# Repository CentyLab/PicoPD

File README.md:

# PicoPD
Pico PD is a development board for USB Power Delivery development with Raspberry Pi Pico footprint. The board can help you negotiate voltage from USB PD 2.0, 3.0, and 3.1 with PPS (programable power supply) up to 5A of current at 20V max. The board feature input current/voltage/temperture reading as well as power switch to cut of the current to external devices.

# Quick links
[AP33772 Library](https://github.com/CentyLab/AP33772-Cpp)

[PicoPD Pinout](#picopd-pinout)

[Setup for AP33772 objects](#setup-for-ap33772-objects)

[Basic AP33772 functions](#basic-ap33772-functions)

[Important note](#important-note)

[Arduino IDE setup](#arduino-ide-setup)

[VSCode PlatformIO setup](#vscode-platformio-setup)

[Enable Serial print for debugging](#enable-serial-debug)

# Pin out

# Setup for AP33772 objects
To use AP33772 IC with the library, first you need to create a `usbpd` object. Then set up your I2C pins and start collecting the power profiles from your charger. Ensure your delay after `Wire.begin()` is more than 500ms for stable PDOs request. Enable pin 23 to allow VBUS pass-through.
```
AP33772 usbpd; // Automatically wire to Wire0

void setup()
{
  Wire.setSDA(0); // Set the correct SDA0 pin
  Wire.setSCL(1); // Set the correct SCL0 pin
  Wire.begin();
  Serial.begin(115200);
  delay(1000); 		// Delay is needed for the IC to obtain PDOs
  usbpd.begin(); 	// Start pulling the PDOs from power supply

  pinMode(25, OUTPUT); // Built in LED
  pinMode(23, OUTPUT); // Load Switch
  digitalWrite(23, HIGH); // Turn on VBUS pin

  usbpd.printPDO(); //Print out PDO to Serial port
}
```

# Basic AP33772 functions
Common functions are:
```
setVoltage(int targetVoltage)       //Set voltage, unit in mV, read libary for logic flow
setMaxCurrent(int targetMaxCurrent) //Allow current limit if source has that capability
readVoltage()                       //Return voltage in mV
readCurrent()                       //Return current in mA
printPDO()                          //Print out PDOs in Serial
```

Set over tempearture protection
```
usbpd.setOTPTHR(100);               //Turn off output if NTC detect 100C or above
usbpd.setMask(OTP_EN);              //Enable Over Temp Protection flag
```

# Important note
After flashing, the latest AP33772-CPP has been updated to auto request PDO after bootup without reconnecting the charger. Thank to @Patronics contribution.

Calling `usbpd.printPDO()` without `Serial.begin()` can soft-brick your PicoPD. Causing the IC to be non-recognizable by your computer. You will have to use PicoProbe to reflash the chip. Check out @Patronics [PicoProbePCB](https://github.com/Patronics/PicoProbePCB) if you would like to make a stable fixture for firmware debugging.

# Enable Serial Debug

To enable Serial debug, there are 3 main methods:

**Using USB-C Power/Data splitter (easiest):** Use a USB-C Splitter that separates the USB 2.0 signal into another USB-C port. You only need USB 2.0 FullSpeed (12Mbps) for the job, but never hurts to get extra speed if needed later. 

* [USB-C Power/Data Splitter](https://lectronz.com/products/usb-c-splitter) (USB-HighSpeed)
* [USB-C PD Power Splitter](https://www.tindie.com/products/essenceeng/usb-c-pd-power-splitter/) (USB-HighSpeed)

**Using the provided solder pads at the back:** Desolder the front "USB Jumper" resistors. They are just 2x 0 Ohm resistors that bridge between the RP2040 IC and the USB-C port. Then use a [USB Type A Plug Breakout Cable](https://www.adafruit.com/product/4448?gclid=Cj0KCQjwoK2mBhDzARIsADGbjeo7nigl8f-8mf8ojsnPvi8TiROBC7YXmMKpGVau8VJHeIO8NyU5nncaAs9qEALw_wcB), or make your own from any USB cable and connect to the existing pad at the back of PicoPD

**Using UART communication**: Make sure you are not using GP0 and GP1 as they are reserved for I2C0 channel for AP33772 IC. Check out Youtube tutorial: [Talk to Your Pico Over Serial](https://www.youtube.com/watch?v=pbWhoJdYA1s)

# Arduino IDE setup
Open Arduino IDE, select File -> Preference

Copy this line below and place in "Aditional Boards Manager URLs" -> OK. This will allow you to pull the Earlephilhower Pico core that work with the AP33772 library.

```
https://github.com/earlephilhower/arduino-pico/releases/download/global/package_rp2040_index.json
```

From Board Manager, search for "Pico" and install the "Raspberry Pi Pico/RP2040" core by Earlephilhower

Now from Tool -> Board -> Raspberry Pi Pico/RP2040 -> Raspberry Pi Pico

Now download the latest AP33772 library as a Zip file

```
https://github.com/CentyLab/AP33772-Cpp
```

Import the AP33772 library into your Arduino IDE. Sketch -> Include library -> Add .ZIP Library ...

Now you start using the Example code in File -> Examples -> AP33772-Cpp-main. The example is ready to compile and flash on to your PicoPD.

Now you can plug in your USB-C cable with Power Delivery 2.0/3.0/3.1. If you also like to have serial print out, check out [Enable Serial print for debugging](#enable-serial-debug).

# VSCode PlatformIO setup
After [VSCode](https://code.visualstudio.com/) installation, you will need to install PlatformIO extension.

Now create a new PlatformIO project
+ Name:WhatEverYouWantToCallit
+ Board: Pico (RasberryPi)
+ Framework: Arduino (default)

Click "Finish"

In your new project, copy this and replace everything in platformio.ini. This is how you ask PlatformIO to compile using Earlephilhower Pico core, and enable upload via USB.

```
[env:pico]
platform = https://github.com/maxgerhardt/platform-raspberrypi.git
board = pico
framework = arduino
board_build.core = earlephilhower

;; If directly upload from PC
upload_protocol = picotool
```

Now download the latest AP33772 library as a Zip file. Unzip and place the folder in `lib`

```
https://github.com/CentyLab/AP33772-Cpp
```

Your lib folder should look like this

To try out example code, you copy the content inside `lib/Compiled for PicoPD/PPSCycling/PPSCycling.ino`, And replace everything in your `src/main.cpp`

Now you can plug the PicoPD to your computer via USB-C and hit the upload button. After this, you will have to connect a charger to PicoPD to see the voltage cycling example. If you also like to have serial print out, check out [Enable Serial print for debugging](#enable-serial-debug).

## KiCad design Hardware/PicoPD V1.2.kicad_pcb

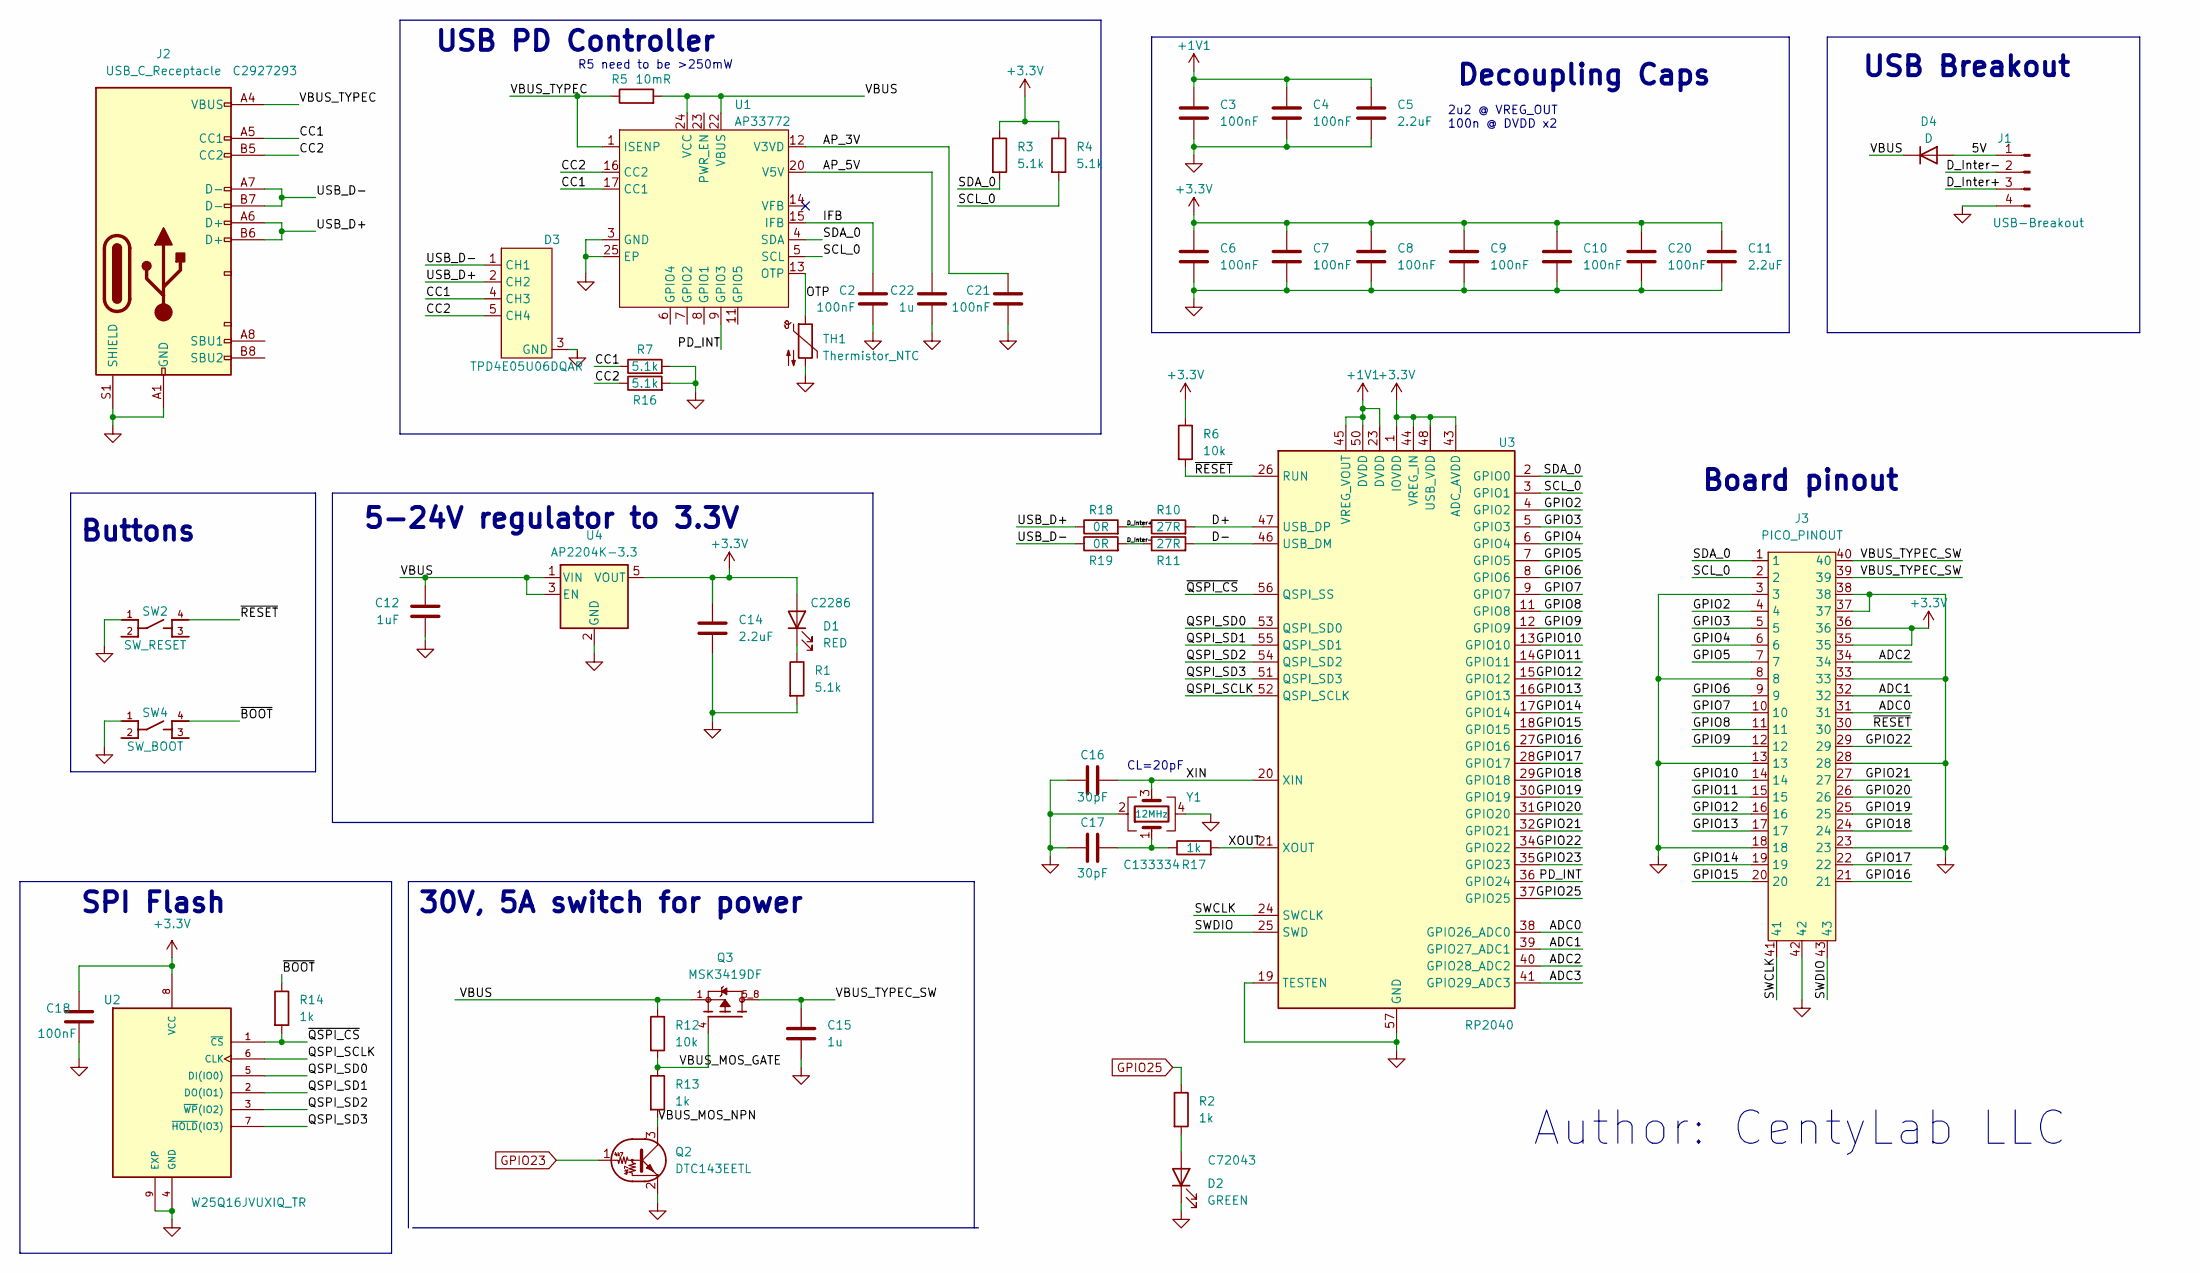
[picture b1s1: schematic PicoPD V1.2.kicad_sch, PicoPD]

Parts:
C2, C3, C4, C6, C7, C8, C9, C10, C18, C20, C21: 100nF; C_0402_1005Metric; LCSC C1525
C5, C11: 2.2uF; C_0402_1005Metric; LCSC C12530
C12: 1uF; C_0603_1608Metric; Voltage 50V; LCSC C15849
C14: 2.2uF; C_0603_1608Metric; Voltage 16V; LCSC C23630
C15, C22: 1u; C_0603_1608Metric; LCSC C15849
C16, C17: 30pF; C_0402_1005Metric; LCSC C1570
D1: RED; LED_0603_1608Metric; LCSC C2286
D2: GREEN; LED_0603_1608Metric; LCSC C72043
D3: TPD4E05U06DQAR; SON50P100X255X50-10N; LCSCAlternative1 C478014
D4: D; D_SOD-123; LCSC C8598
J1: USB-Breakout; 1x4_2.54mmHorizontalSMD
J2: USB_C_Receptacle; YTC-TC16S-28; LCSC C2927293
J3: PICO_PINOUT; PICO_Thru
Q2: DTC143EETL; SOT-416; LCSC C2991940
Q3: MSK3419DF; TRANS_AON7403; PARTREV G; LCSC C2902915
R1, R3, R4, R7, R16: 5.1k; R_0402_1005Metric; LCSC C25905
R2, R13, R14, R17: 1k; R_0402_1005Metric; LCSC C11702
R5: 10mR; R_0805_2012Metric; LCSC C728271
R6, R12: 10k; R_0402_1005Metric; LCSC C25744
R10, R11: 27R; R_0402_1005Metric; LCSC C138021
R18, R19: 0R; R_0402_1005Metric; LCSC C17168
SW2: SW_RESET; SW_PTS810_SJM_250_SMTR_LFS; LCSC C221896
SW4: SW_BOOT; SW_PTS810_SJM_250_SMTR_LFS; LCSC C221896
TH1: Thermistor_NTC; R_0402_1005Metric; LCSC C77131
U1: AP33772; QFN-24-1EP_4x4mm_P0.5mm_EP2.6x2.6mm
U2: W25Q16JVUXIQ_TR; IC_W25Q16JVUXIQ_TR; PARTREV H; LCSC C2843335
U3: RP2040; QFN-56-1EP_7x7mm_P0.4mm_EP3.2x3.2mm; LCSC C2040
U4: AP2204K-3.3; SOT-23-5; JLCPCB Rotation Offset 180
Y1: 12MHz; Crystal_SMD_3225-4Pin_3.2x2.5mm; LCSC C133334

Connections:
+1V1: C3.1, C4.1, C5.1, U3.23 (DVDD), U3.45 (VREG_VOUT), U3.50 (DVDD)
+3.3V: C6.1, C7.1, C8.1, C9.1, C10.1, C11.1, C14.1, C18.1, C20.1, D1.2 (A), J3.35, J3.36, R3.1, R4.1, R6.1, U2.8 (VCC), U3.1 (IOVDD), U3.10 (IOVDD), U3.22 (IOVDD), U3.33 (IOVDD), U3.42 (IOVDD), U3.43 (ADC_AVDD), U3.44 (VREG_IN), U3.48 (USB_VDD), U3.49 (IOVDD), U4.5 (VOUT)
/5V: D4.2 (A), J1.1
/ADC0: J3.31, U3.38 (GPIO26_ADC0)
/ADC1: J3.32, U3.39 (GPIO27_ADC1)
/ADC2: J3.34, U3.40 (GPIO28_ADC2)
/ADC3: U3.41 (GPIO29_ADC3)
/AP_3V: C21.1, U1.12 (V3VD)
/AP_5V: C22.1, U1.20 (V5V)
/CC1: D3.4 (CH3), D3.7, J2.A5 (CC1), R7.1, U1.17 (CC1)
/CC2: D3.5 (CH4), D3.6, J2.B5 (CC2), R16.1, U1.16 (CC2)
/D+: R10.2, U3.47 (USB_DP)
/D-: R11.2, U3.46 (USB_DM)
/D_Inter+: J1.3, R10.1, R18.2
/D_Inter-: J1.2, R11.1, R19.2
/GPIO2: J3.4, U3.4 (GPIO2)
/GPIO3: J3.5, U3.5 (GPIO3)
/GPIO4: J3.6, U3.6 (GPIO4)
/GPIO5: J3.7, U3.7 (GPIO5)
/GPIO6: J3.9, U3.8 (GPIO6)
/GPIO7: J3.10, U3.9 (GPIO7)
/GPIO8: J3.11, U3.11 (GPIO8)
/GPIO9: J3.12, U3.12 (GPIO9)
/GPIO10: J3.14, U3.13 (GPIO10)
/GPIO11: J3.15, U3.14 (GPIO11)
/GPIO12: J3.16, U3.15 (GPIO12)
/GPIO13: J3.17, U3.16 (GPIO13)
/GPIO14: J3.19, U3.17 (GPIO14)
/GPIO15: J3.20, U3.18 (GPIO15)
/GPIO16: J3.21, U3.27 (GPIO16)
/GPIO17: J3.22, U3.28 (GPIO17)
/GPIO18: J3.24, U3.29 (GPIO18)
/GPIO19: J3.25, U3.30 (GPIO19)
/GPIO20: J3.26, U3.31 (GPIO20)
/GPIO21: J3.27, U3.32 (GPIO21)
/GPIO22: J3.29, U3.34 (GPIO22)
/IFB: C2.1, U1.15 (IFB)
/OTP: TH1.1, U1.13 (OTP)
/PD_INT: U1.9 (GPIO3), U3.36 (GPIO24)
/QSPI_SCLK: U2.6 (CLK), U3.52 (QSPI_SCLK)
/QSPI_SD0: U2.5 (DI(IO0)), U3.53 (QSPI_SD0)
/QSPI_SD1: U2.2 (DO(IO1)), U3.55 (QSPI_SD1)
/QSPI_SD2: U2.3 (~WP(IO2)), U3.54 (QSPI_SD2)
/QSPI_SD3: U2.7 (~HOLD(IO3)), U3.51 (QSPI_SD3)
/SCL_0: J3.2, R4.2, U1.5 (SCL), U3.3 (GPIO1)
/SDA_0: J3.1, R3.2, U1.4 (SDA), U3.2 (GPIO0)
/SWCLK: J3.41, U3.24 (SWCLK)
/SWDIO: J3.43, U3.25 (SWD)
/USB_D+: D3.2 (CH2), D3.9, J2.A6 (D+), J2.B6 (D+), R18.1
/USB_D-: D3.1 (CH1), D3.10, J2.A7 (D-), J2.B7 (D-), R19.1
/VBUS: C12.2, D4.1 (K), Q3.1, Q3.2, Q3.3, R5.2, R12.1, U1.22 (VBUS), U1.24 (VCC), U4.1 (VIN), U4.3 (EN)
/VBUS_MOS_GATE: Q3.4, R12.2, R13.1
/VBUS_MOS_NPN: Q2.3 (C), R13.2
/VBUS_TYPEC: J2.A4 (VBUS), J2.A9 (VBUS), J2.B4 (VBUS), J2.B9 (VBUS), R5.1, U1.1 (ISENP)
/VBUS_TYPEC_SW: C15.1, J3.39, J3.40, Q3.5_8
/XIN: C16.1, U3.20 (XIN), Y1.3
/XOUT: R17.2, U3.21 (XOUT)
/~BOOT: R14.1, SW4.4
/~QSPI_CS: R14.2, U2.1 (~CS), U3.56 (QSPI_SS)
/~RESET: J3.30, R6.2, SW2.4, U3.26 (RUN)
GND: C2.2, C3.2, C4.2, C5.2, C6.2, C7.2, C8.2, C9.2, C10.2, C11.2, C12.1, C14.2, C15.2, C16.2, C17.2, C18.2, C20.2, C21.2, C22.2, D2.1 (K), D3.3 (GND), D3.8 (GND), J1.4, J2.A1 (GND), J2.A12 (GND), J2.B1 (GND), J2.B12 (GND), J2.S1 (SHIELD), J3.3, J3.8, J3.13, J3.18, J3.23, J3.28, J3.33, J3.37, J3.38, J3.42, Q2.2 (E), R1.2, R7.2, R16.2, SW2.1, SW4.1, TH1.2, U1.3 (GND), U1.25 (EP), U2.4 (GND), U2.9 (EXP), U3.19 (TESTEN), U3.57 (GND), U4.2 (GND), Y1.2, Y1.4
GPIO23: Q2.1 (B), U3.35 (GPIO23)
GPIO25: R2.1, U3.37 (GPIO25)
unnamed: C17.1, R17.1, Y1.1
unnamed: D1.1 (K), R1.1
unnamed: D2.2 (A), R2.2
unnamed: U1.2 (NC), U1.10 (NC), U1.18 (NC), U1.19 (NC), U1.21 (NC)

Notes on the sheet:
USB PD Controller
2u2 @ VREG_OUT 100n @ DVDD x2
30V, 5A switch for power
USB Breakout
CL=20pF
Author: CentyLab LLC
Buttons
Decoupling Caps
5-24V regulator to 3.3V
SPI Flash
Board pinout
R5 need to be >250mW

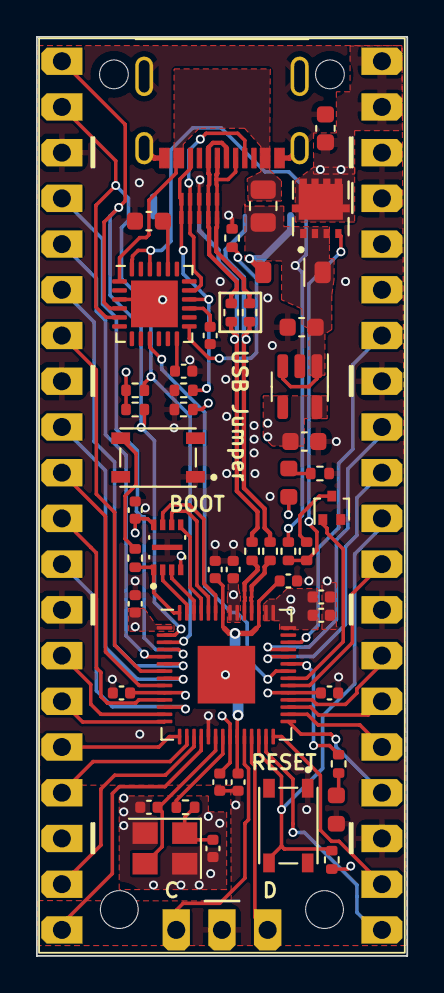
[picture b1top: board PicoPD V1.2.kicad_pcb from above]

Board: 4 copper layers, 20.6 x 51.1 mm, 52 parts (1 on the bottom side), 66 nets.

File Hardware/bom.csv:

Designator,Footprint,Quantity,Value,LCSC Part #
"C10, C18, C2, C20, C21, C3, C4, C6, C7, C8, C9",0402,11,100nF,C1525
"C11, C5",0402,2,2.2uF,C12530
C12,0603,1,1uF,C15849
C14,0603,1,2.2uF,C23630
"C15, C22",0603,2,1u,C15849
"C16, C17",0402,2,30pF,C1570
D1,0603,1,RED,C2286
D2,0603,1,GREEN,C72043
D3,SON50P100X255X50-10N,1,TPD4E05U06DQAR,C138714
D4,D_SOD-123,1,D,C8598
J2,YTC-TC16S-28,1,USB_C_Receptacle,C2927293
Q2,SOT-416,1,DTC143EETL,C2991940
Q3,TRANS_AON7403,1,MSK3419DF,C2902915
"R1, R16, R3, R4, R7",0402,5,5.1k,C25905
"R10, R11",0402,2,27R,C138021
"R12, R6",0402,2,10k,C25744
"R13, R14, R17, R2",0402,4,1k,C11702
"R18, R19",0402,2,0R,C17168
R5,0805,1,10mR,C728271
SW2,SW_PTS810_SJM_250_SMTR_LFS,1,SW_RESET,C221896
SW4,SW_PTS810_SJM_250_SMTR_LFS,1,SW_BOOT,C221896
TH1,0402,1,Thermistor_NTC,C77131
U1,QFN-24-1EP_4x4mm_P0.5mm_EP2.6x2.6mm,1,AP33772,C5244513
U2,IC_W25Q16JVUXIQ_TR,1,W25Q16JVUXIQ_TR,C2843335
U3,QFN-56-1EP_7x7mm_P0.4mm_EP3.2x3.2mm,1,RP2040,C2040
U4,SOT-23-5,1,AP2204K-3.3,C112032
Y1,Crystal_SMD_3225-4Pin_3.2x2.5mm,1,12MHz,C133334

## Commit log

2024-02-09 Update documentation
2024-02-25 Update serial read method
2024-03-09 Added dimensions
2024-03-12 Add AP33772 code as submodule
2024-03-16 Update USB C splitter link
2024-06-10 Update AP33772 Submodule
2024-08-11 Added BOM and Pick-N-Place
2024-12-04 Add VScode tutorial
2024-12-04 Correct spelling
2024-12-04 Update Software
